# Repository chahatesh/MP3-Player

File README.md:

# MP3 Player

A small, custom MP3 player I designed using an ESP32-S3-Zero, DFPlayer Mini, TFT display, and a rotary encoder.

I wanted to make a simple music player becouse playing music on my phone is Data intensive. I designed the PCB in KiCad and also made a 3D-printable case for it.

The player uses a microSD card to store music, a rotary encoder to switch songs, and a small TFT display that shows the current song number and whether the music is playing or paused.

## Images

## Features

- ESP32-S3-Zero microcontroller
- DFPlayer Mini for MP3 playback
- Small TFT display for song number and playback status
- Rotary encoder for controlling music
- 3.5mm audio jack
- Custom PCB designed in KiCad
- 3D-printable case and encoder cap
- Music stored on a microSD card

## How It Works

The ESP32 controls the DFPlayer Mini through a serial connection. The DFPlayer reads MP3 files from a microSD card and handles audio playback.

A rotary encoder is used to control the songs turning it changes the song, and clicking it plays or pauses it.

The TFT display is kept simple. It only shows the current song number and whether the player is playing or paused.

## Pin Connections

The current Arduino code uses the following GPIO pins.

### TFT Display

| TFT Pin | ESP32 GPIO |
|---|---|
| CS | GPIO10 |
| DC | GPIO9 |
| RST | GPIO13 |
| SCK | GPIO12 |
| MOSI | GPIO11 |

### Rotary Encoder

| Encoder Pin | ESP32 GPIO |
|---|---|
| A | GPIO6 |
| B | GPIO7 |
| Switch | GPIO8 |
| Common | GND |

### DFPlayer Mini

The ESP32 TX pin (GPIO43) connects to the DFPlayer RX pin through a 1kΩ resistor.

The ESP32 and DFPlayer also share a common ground.

The DFPlayer's left and right outputs connect to the audio jack through the PCB.

## PCB Design

I designed the PCB using KiCad. The main goal was to fit all the components into a small board while keeping everything organized.

The board includes connections for the ESP32, TFT display, DFPlayer Mini, rotary encoder, and audio jack.

The KiCad project files are included in the repository:

- [PCB Layout](MP3-Player.kicad_pcb)
- [Schematic](MP3-Player.kicad_sch)
- [KiCad Project](MP3-Player.kicad_pro)

Manufacturing files are available in the [production](production) folder, including a Gerber for PCB fabrication.

## 3D Printed Case

I also designed a case to hold the PCB and a cap for the rotary encoder.

The files are available in both STL and STEP formats:

| Part | STL | STEP |
|---|---|---|
| PCB Case | [Download](CAD/PCB-Case.stl) | [Download](CAD/PCB-Case.step) |
| Rotary Encoder Cap | [Download](CAD/RE-Cap.stl) | [Download](CAD/RE-Cap.step) |

The STL files can be used for 3D printing, while the STEP files can be edited in CAD software.

I used Onshape for this, link [Here](https://cad.onshape.com/documents/7a1423e237ed7c255f250c8c/w/72b5ca8bb9bfd8214d66d290/e/8e44508844e352792cba2dbb?renderMode=0&uiState=6ae691a64f304a127a6a8070)

## Building Your Own

### 1. Order the PCB

Download the manufacturing ZIP from the [production folder](production/MP3-Player.zip) and upload it to a PCB manufacturer.

### 2. Get the Components

Use the component list and BOM to get the required parts.

### 3. Assemble the Board

Solder the headers, resistor, rotary encoder, audio jack, and other required components onto the PCB.

Connect the ESP32, TFT display, and DFPlayer Mini.

Check the power and ground connections before turning it on.

### 4. Upload the Code

Open [MP3-player-code.ino](MP3-player-code.ino) in Arduino IDE.

Install these libraries:

- Adafruit GFX Library
- Adafruit ST7735 and ST7789 Library
- DFRobotDFPlayerMini

Install ESP32 board support, select the appropriate ESP32-S3 board configuration, and upload the sketch.

The code is configured for an ST7735 display. Other display models may require changes.

### 5. Add Music

Format a microSD card as FAT32 and create a folder named `mp3`.

Name your files `0001.mp3`, `0002.mp3`, `0003.mp3`, and so on.

The current code is configured for 10 songs. You can change SONG_COUNT in the Arduino code to match the number of tracks on the card.

### 6. Test It

Power the player and test the rotary encoder.

Turning it should change songs, and pressing it should pause or resume playback.

The screen displays the song number and the playback state requested by the ESP32. It does not independently verify that audio is playing.

The goal was to build a simple, compact music player using my own PCB instead of connecting everything with a breadboard.

Designed by [Chahatesh](https://github.com/chahatesh).

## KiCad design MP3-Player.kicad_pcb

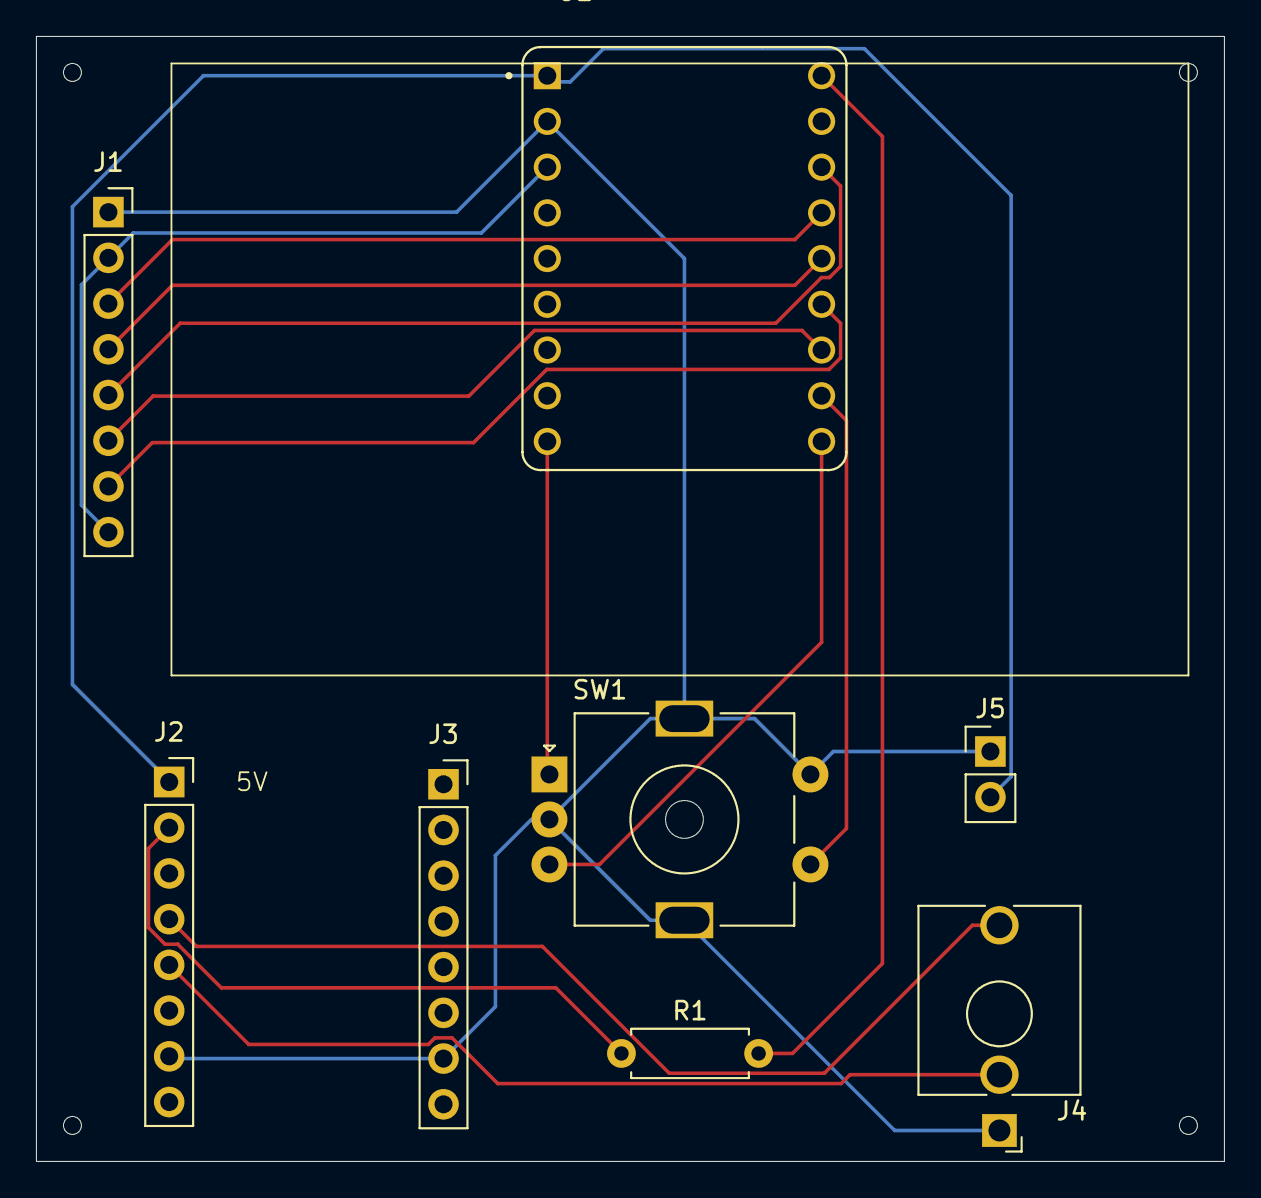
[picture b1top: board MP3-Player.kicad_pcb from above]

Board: 2 copper layers, 66.0 x 62.5 mm, 8 parts (0 on the bottom side), 15 nets.

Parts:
J1, J2, J3: Conn_01x08_Socket; PinSocket_1x08_P2.54mm_Vertical
J4: AudioJack3; Jack_3.5mm_QingPu_WQP-PJ398SM_Vertical_CircularHoles
J5: Conn_01x02_Pin; PinHeader_1x02_P2.54mm_Vertical
R1: 1kΩ; R_Axial_DIN0207_L6.3mm_D2.5mm_P7.62mm_Horizontal
SW1: RotaryEncoder_Switch_MP; RotaryEncoder_Alps_EC11E-Switch_Vertical_H20mm_MountingHoles
U1: Waveshare ESP32-S3-ZERO; Waveshare ESP32-S3-Zero

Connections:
/3.3V: J1.2, J1.8, U1.3V3 (3V3(OUT))
/5v: J2.1, J5.2, U1.5V
/DAC_L: J2.5, J4.TN
/DAC_R: J2.4, J4.T
/G6: SW1.A, U1.6 (GP6)
/G7: SW1.B, U1.7 (GP7)
/G8: SW1.S1, U1.8 (GP8)
/GND: J1.1, J2.7, J3.7 (Pin_7_7), J4.S, J5.1, SW1.C, SW1.MP, SW1.S2, U1.GND
/RX: J2.2, R1.1
unnamed: J1.3, U1.12 (GP12)
unnamed: J1.4, U1.11 (GP11)
unnamed: J1.5, U1.13 (GP13)
unnamed: J1.6, U1.9 (GP9)
unnamed: J1.7, U1.10 (GP10)
unnamed: R1.2, U1.TX
